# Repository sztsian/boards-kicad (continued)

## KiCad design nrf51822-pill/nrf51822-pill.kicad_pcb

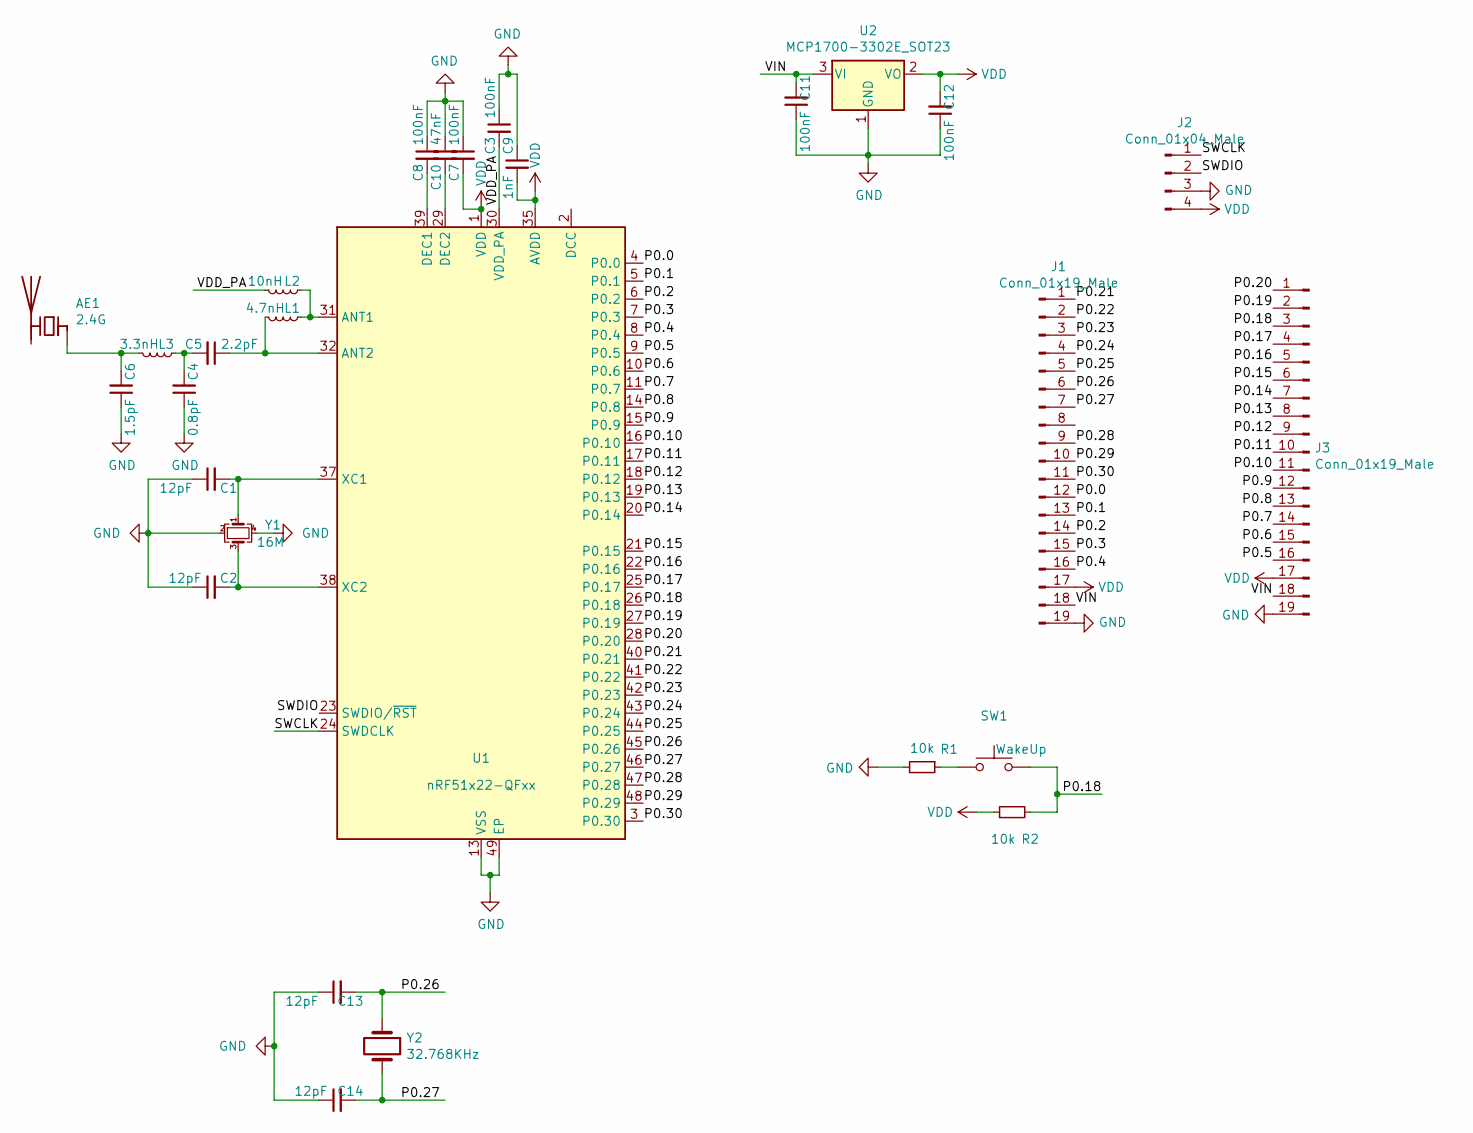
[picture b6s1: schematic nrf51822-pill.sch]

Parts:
AE1: 2.4G; Texas_SWRA117D_2.4GHz_Left
C1, C2, C13, C14: 12pF; C_0603_1608Metric
C3, C7, C8, C11, C12: 100nF; C_0603_1608Metric
C4: 0.8pF; C_0603_1608Metric
C5: 2.2pF; C_0603_1608Metric
C6: 1.5pF; C_0603_1608Metric
C9: 1nF; C_0603_1608Metric
C10: 47nF; C_0603_1608Metric
J1, J3: Conn_01x19_Male; PinHeader_1x19_P2.54mm_Vertical
J2: Conn_01x04_Male; PinHeader_1x04_P2.54mm_Vertical
L1: 4.7nH; L_0603_1608Metric
L2: 10nH; L_0603_1608Metric
L3: 3.3nH; L_0603_1608Metric
R1, R2: 10k; R_0603_1608Metric
SW1: WakeUp; smd_push
U1: nRF51x22-QFxx; QFN-48-1EP_6x6mm_P0.4mm_EP4.6x4.6mm
U2: MCP1700-3302E_SOT23; SOT-23
Y1: 16M; Crystal_SMD_2520-4Pin_2.5x2.0mm
Y2: 32.768KHz; Crystal_SMD_3215-2Pin_3.2x1.5mm

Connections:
/P0.0: J1.12, U1.4 (P0.0)
/P0.1: J1.13, U1.5 (P0.1)
/P0.2: J1.14, U1.6 (P0.2)
/P0.3: J1.15, U1.7 (P0.3)
/P0.4: J1.16, U1.8 (P0.4)
/P0.5: J3.16, U1.9 (P0.5)
/P0.6: J3.15, U1.10 (P0.6)
/P0.7: J3.14, U1.11 (P0.7)
/P0.8: J3.13, U1.14 (P0.8)
/P0.9: J3.12, U1.15 (P0.9)
/P0.10: J3.11, U1.16 (P0.10)
/P0.11: J3.10, U1.17 (P0.11)
/P0.12: J3.9, U1.18 (P0.12)
/P0.13: J3.8, U1.19 (P0.13)
/P0.14: J3.7, U1.20 (P0.14)
/P0.15: J3.6, U1.21 (P0.15)
/P0.16: J3.5, U1.22 (P0.16)
/P0.17: J3.4, U1.25 (P0.17)
/P0.18: J3.3, R2.2, SW1.2, U1.26 (P0.18)
/P0.19: J3.2, U1.27 (P0.19)
/P0.20: J3.1, U1.28 (P0.20)
/P0.21: J1.1, U1.40 (P0.21)
/P0.22: J1.2, U1.41 (P0.22)
/P0.23: J1.3, U1.42 (P0.23)
/P0.24: J1.4, U1.43 (P0.24)
/P0.25: J1.5, U1.44 (P0.25)
/P0.26: C13.2, J1.6, U1.45 (P0.26), Y2.1
/P0.27: C14.2, J1.7, U1.46 (P0.27), Y2.2
/P0.28: J1.9, U1.47 (P0.28)
/P0.29: J1.10, U1.48 (P0.29)
/P0.30: J1.11, U1.3 (P0.30)
/SWCLK: J2.1, U1.24 (SWDCLK)
/SWDIO: J2.2, U1.23 (SWDIO/~RST)
/VDD_PA: C3.2, L2.2, U1.30 (VDD_PA)
/VIN: C11.2, J1.18, J3.18, U2.3 (VI)
GND: C1.1, C2.1, C3.1, C4.1, C6.1, C7.1, C8.1, C9.1, C10.1, C11.1, C12.1, C13.1, C14.1, J1.19, J2.3, J3.19, R1.2, U1.13 (VSS), U1.33 (VSS), U1.34 (VSS), U1.49 (EP), U2.1 (GND), Y1.2, Y1.4
unnamed: AE1.1 (FEED), C6.2, L3.2
unnamed: C1.2, U1.37 (XC1), Y1.1
unnamed: C2.2, U1.38 (XC2), Y1.3
unnamed: C4.2, C5.2, L3.1
unnamed: C5.1, L1.2, U1.32 (ANT2)
unnamed: C8.2, U1.39 (DEC1)
unnamed: C10.2, U1.29 (DEC2)
unnamed: L1.1, L2.1, U1.31 (ANT1)
unnamed: R1.1, SW1.1
VDD: C7.2, C9.2, C12.2, J1.17, J2.4, J3.17, R2.1, U1.1 (VDD), U1.12 (VDD), U1.35 (AVDD), U1.36 (AVDD), U2.2 (VO)

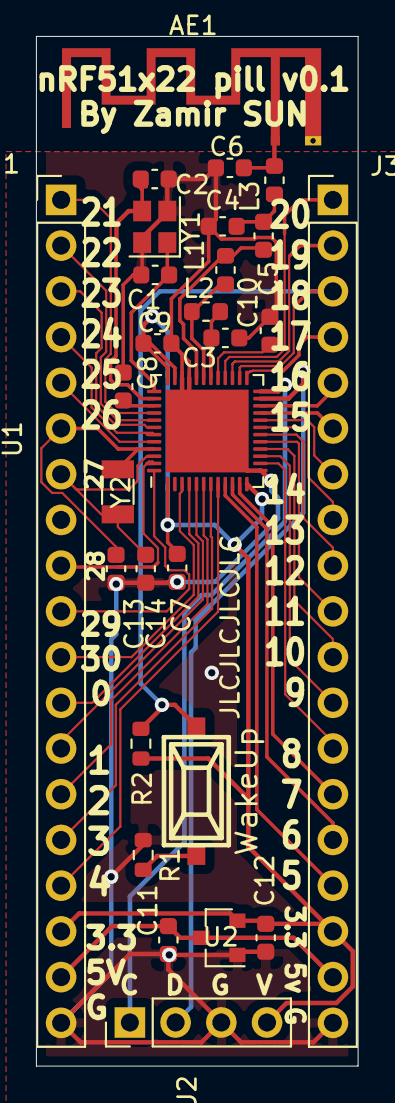
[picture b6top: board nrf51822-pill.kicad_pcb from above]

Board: 2 copper layers, 17.9 x 57.2 mm, 28 parts (0 on the bottom side), 46 nets.

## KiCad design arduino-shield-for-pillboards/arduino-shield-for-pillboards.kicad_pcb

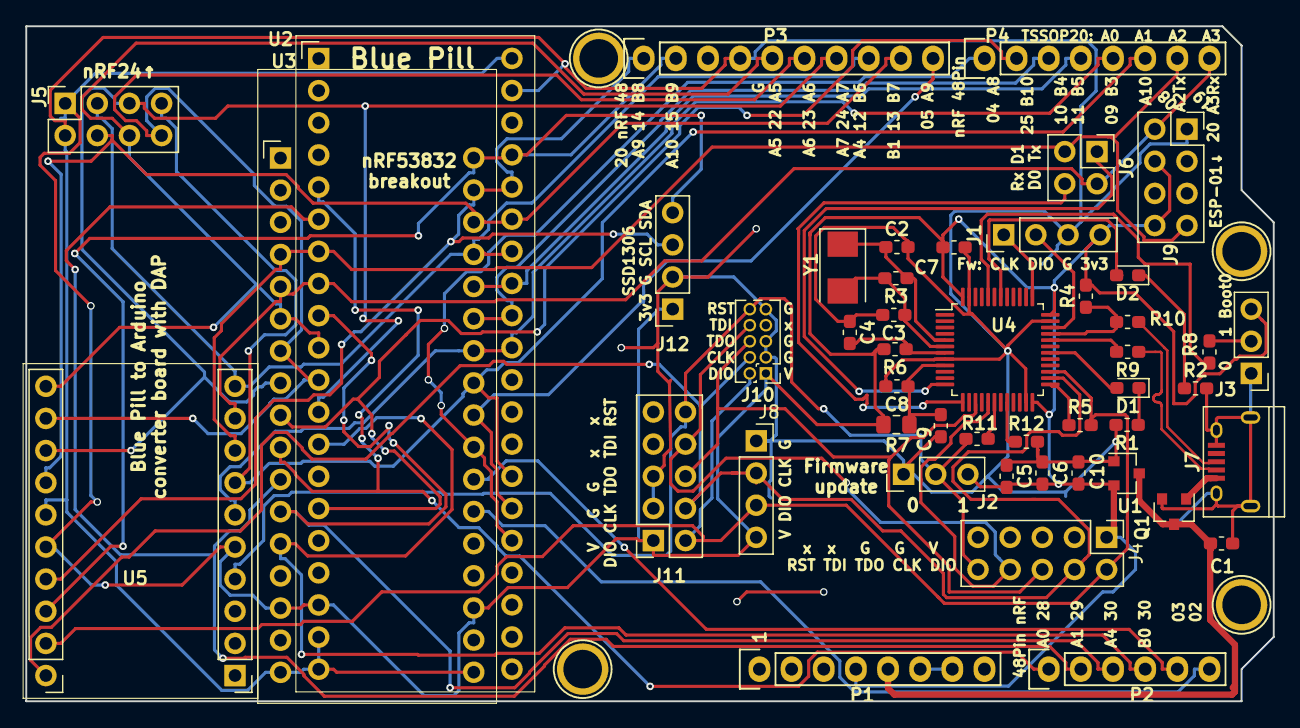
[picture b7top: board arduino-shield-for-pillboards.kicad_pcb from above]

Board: 2 copper layers, 98.6 x 53.3 mm, 51 parts (0 on the bottom side), 52 nets.

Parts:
C1, C4: C_Small; C_0603_1608Metric_Pad1.05x0.95mm_HandSolder
C2, C3: 20p; C_0603_1608Metric_Pad1.05x0.95mm_HandSolder
C5, C6, C7: 0.1u; C_0603_1608Metric_Pad1.05x0.95mm_HandSolder
C8: 10n; C_0603_1608Metric_Pad1.05x0.95mm_HandSolder
C9: 2.2u; C_0603_1608Metric_Pad1.05x0.95mm_HandSolder
C10: 100nF; C_0603_1608Metric_Pad1.05x0.95mm_HandSolder
D1: LED_RUN; LED_0603_1608Metric_Pad1.05x0.95mm_HandSolder
D2: LED_CON; LED_0603_1608Metric_Pad1.05x0.95mm_HandSolder
J1: IF_SWD; PinHeader_1x04_P2.54mm_Vertical
J2: UpdateFW; PinHeader_1x03_P2.54mm_Vertical
J3: Boot0; PinHeader_1x03_P2.54mm_Vertical
J4: Conn_ARM_JTAG_SWD_10; PinHeader_2x05_P2.54mm_Vertical
J5: nRF24; PinSocket_2x04_P2.54mm_Vertical
J6: Conn_01x02_Male; PinHeader_2x02_P2.54mm_Vertical
J7: USB_B_Micro; USB_Micro-B_Connector
J8: Blue_Pill_SWD; PinSocket_1x04_P2.54mm_Vertical
J9: ESP-01; PinSocket_2x04_P2.54mm_Vertical
J10: Conn_ARM_JTAG_SWD_10; PinHeader_2x05_P1.27mm_Vertical
J11: TGT_JTAG2; PinSocket_2x05_P2.54mm_Vertical
J12: SSD1306; PinSocket_1x04_P2.54mm_Vertical
P1: Power; Socket_Strip_Arduino_1x08
P2: Analog; Socket_Strip_Arduino_1x06
P3: Digital; Socket_Strip_Arduino_1x10
P4: Digital; Socket_Strip_Arduino_1x08
P5, P6, P7, P8: CONN_01X01; Arduino_1pin
Q1: Si2305(A5); SOT-23
R1, R2, R6, R8, R11, R12: 10k; R_0603_1608Metric_Pad1.05x0.95mm_HandSolder
R3: 1M; R_0603_1608Metric_Pad1.05x0.95mm_HandSolder
R4: 1.5K; R_0603_1608Metric_Pad1.05x0.95mm_HandSolder
R5: 100; R_0603_1608Metric_Pad1.05x0.95mm_HandSolder
R7: 0R; R_0805_2012Metric_Pad1.15x1.40mm_HandSolder
R9, R10: 22; R_0603_1608Metric_Pad1.05x0.95mm_HandSolder
U1: MCP1700-3302E_SOT23; SOT-23
U2: BluePill
U3: nRF52832-Breakout; nRF52832_Breakout
U4: STM32F103C8Tx; LQFP-48_7x7mm_P0.5mm
U5: STM32F0-TSSOP20-board; TSSOP20-board
Y1: 8M; Crystal_SMD_5032-2Pin_5.0x3.2mm

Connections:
3V3: C5.2, C6.2, C7.2, C10.1, J1.4, J2.3, J3.3, J4.1, J5.1, J8.4, J9.4, J9.8, J10.1, J11.1, J12.1, P1.4, R4.2, R6.2, R7.1, U1.2, U2.18, U2.40, U3.15, U3.20, U4.24, U4.36, U4.48, U5.5, U5.16
5V: C1.1, P1.5, Q1.3, U1.3
A0: P2.1, U2.5, U3.10
A1: P2.2, U2.6, U3.11
A2: P2.3, U2.9, U3.12
A3: P2.4, U2.13, U3.13
A4: P2.5, U3.24
A5: P2.6, U3.23
BOOT0: J3.2, R8.2
D0(Rx): J6.2, J9.2, P4.8, U2.8, U3.5, U5.9
D1(Tx): J6.3, J9.7, P4.7, U2.7, U3.4, U5.8
D2: J5.7, P4.6, U2.27, U3.27, U5.7
D3: P4.5, U2.31, U3.28, U5.6
D4: P4.4, U2.33, U3.30
D5: P4.3, U2.32, U3.29
D6: P4.2, U2.15, U3.9
D7: P4.1, U2.25, U3.25
D8: P3.10, U2.26, U3.26
D9: J5.4, P3.9, U2.35, U3.32, U5.14
D10: J5.3, P3.8, U2.34, U3.31, U5.10
D11: J5.5, P3.7, U2.12, U3.8, U5.13
D12: J5.8, P3.6, U2.11, U3.7, U5.12
D13: J5.6, P3.5, U2.10, U3.6, U5.11
GND: C1.2, C2.2, C3.2, C4.1, C5.1, C6.1, C7.1, C8.2, C9.2, C10.2, J1.3, J2.1, J3.1, J4.3, J4.5, J4.9, J5.2, J7.5, J7.6, J8.1, J9.1, J10.3, J10.5, J10.9, J11.3, J11.5, J12.2, P1.6, P1.7, P3.4, Q1.2, R1.2, R2.2, R12.2, U1.1, U2.19, U2.20, U2.39, U3.17, U3.18, U4.8, U4.23, U4.35, U4.47, U5.15
unnamed: C2.1, R3.1, U4.5, Y1.1
unnamed: C3.1, R3.2, U4.6, Y1.2
unnamed: C4.2, R6.1, U4.7
unnamed: C8.1, C9.1, R7.2, U4.9
unnamed: D1.1, R1.1
unnamed: D2.1, R2.1
unnamed: J7.1, Q1.1
unnamed: R5.1, U4.25
unnamed: R8.1, U4.44
unnamed: R11.1, U4.18
unnamed: R12.1, U4.20
PA2-UART2-TX: J6.1, U4.12
PA3-UART2-RX: J6.4, U4.13
PA9-LED-RUN: D1.2, U4.30
PA11: R9.2, U4.32
PA12: R4.1, R10.2, U4.33
PA13-SWDIO-TMS: J1.2, U4.34
PA14-SWCLK-TCK: J1.1, U4.37
PB0-nRST: J2.2, J4.10, J10.10, J11.10, R11.2, U5.4
PB6-LED-CON: D2.2, U4.42
SCL: J12.3, P3.1, U2.36, U3.33, U5.17
SDA: J12.4, P3.2, U2.37, U3.34, U5.18
TCK-SWCLK: J4.4, J8.2, J10.4, J11.4, U4.26, U5.20
TDI: J4.8, J10.8, J11.8, U4.17
TDO: J4.6, J10.6, J11.6, U4.15
TMS-SWDIO: J4.2, J8.3, J10.2, J11.2, R5.2, U4.27, U5.19
USB-D+: J7.3, R10.1
USB-D-: J7.2, R9.1

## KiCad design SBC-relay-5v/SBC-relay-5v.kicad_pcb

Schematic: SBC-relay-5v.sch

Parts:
C1, C2: 10uF; C_0603_1608Metric_Pad1.05x0.95mm_HandSolder
C3: 100nF; C_0603_1608Metric_Pad1.05x0.95mm_HandSolder
C4, C5: 22pF; C_0603_1608Metric_Pad1.05x0.95mm_HandSolder
D1, D9: 1N4007; D_0603_1608Metric_Pad1.05x0.95mm_HandSolder
D2: LED_IN; LED_0603_1608Metric_Pad1.05x0.95mm_HandSolder
D3: USB1; LED_0603_1608Metric_Pad1.05x0.95mm_HandSolder
D4: USB2; LED_0603_1608Metric_Pad1.05x0.95mm_HandSolder
D5: USB5; LED_0603_1608Metric_Pad1.05x0.95mm_HandSolder
D6: USB6; LED_0603_1608Metric_Pad1.05x0.95mm_HandSolder
D7: USB3; LED_0603_1608Metric_Pad1.05x0.95mm_HandSolder
D8: USB4; LED_0603_1608Metric_Pad1.05x0.95mm_HandSolder
J1: USB_B_Micro; USB_Micro-B_Connector
J2: PWR_IN; KF762_2P
J3, J4: USB_A_Stacked; USB_A_Wuerth_61400826021_Horizontal_Stacked
J5, J6: USB_A; USB_A_Vertical
K1, K2, K3, K4, K5, K6: SANYOU_SRD_Form_A; Relay_SPST_SANYOU_SRD_Series_Form_A
MK1, MK2, MK3, MK4: M2.5; MountingHole_2.7mm_M2.5
Q1, Q2: S8050; SOT-23_Handsoldering
R1, R3, R4, R5, R6, R8: 10k; R_0603_1608Metric_Pad1.05x0.95mm_HandSolder
R2, R9, R10, R11, R12, R13, R14: 100R; R_0603_1608Metric_Pad1.05x0.95mm_HandSolder
R7: 470; R_0603_1608Metric_Pad1.05x0.95mm_HandSolder
SW1: SW_Flash; smd_push
U1: AP1117-33; SOT-223-3_TabPin2
U2: ESP-12F; ESP-12E
U3: ULN2003; SOIC-16_3.9x9.9mm_P1.27mm
U4: CH340G; SOIC-16_3.9x9.9mm_P1.27mm
Y1: 12M; Crystal_AT310_D3.0mm_L10.0mm_Horizontal

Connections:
3V3_MCU: C2.1, C3.1, Q1.3, R4.2, R5.1, R8.1, U1.2 (VO), U2.1, U2.8, U4.4, U4.16
5V_IN: D9.2, J2.1, K1.1, K2.1, K3.1, K4.1, K5.1, K6.1, R2.1
DTR: Q2.1, R1.1, U4.13
GND_IN: C1.2, C2.2, C3.2, C4.2, C5.2, D2.1 (K), J1.5 (GND), J1.6 (Shield), J2.2, J3.4, J3.8, J3.9, J4.4, J4.8, J4.9, J5.4, J5.5, J6.4, J6.5, R6.1, R9.1, R10.1, R11.1, R12.1, R13.1, R14.1, SW1.2, U1.1 (GND), U2.15, U3.8, U4.1
GPIO0: Q2.3, R7.2, R8.2, U2.18
GPIO4: U2.19, U3.1
GPIO5: U2.20, U3.2
GPIO12: U2.6, U3.3
GPIO13: U2.7, U3.4
GPIO14: U2.5, U3.5
GPIO16: U2.4, U3.6
unnamed: C4.1, U4.7, Y1.1
unnamed: C5.1, U4.8, Y1.2
unnamed: D1.2, J1.1 (VBUS)
unnamed: D2.2 (A), R2.2
unnamed: D3.1 (K), R9.2
unnamed: D3.2 (A), J3.1, K1.3
unnamed: D4.1 (K), R10.2
unnamed: D4.2 (A), J3.5, K2.3
unnamed: D5.1 (K), R11.2
unnamed: D5.2 (A), J5.1, K5.3
unnamed: D6.1 (K), R12.2
unnamed: D6.2 (A), J6.1, K6.3
unnamed: D7.1 (K), R13.2
unnamed: D7.2 (A), J4.1, K3.3
unnamed: D8.1 (K), R14.2
unnamed: D8.2 (A), J4.5, K4.3
unnamed: Q1.2, R1.2
unnamed: Q2.2, R3.2
unnamed: R4.1, U2.3
unnamed: R5.2, U2.17
unnamed: R6.2, U2.16
unnamed: R7.1, SW1.1
RTS: Q1.1, R3.1, U4.14
RXD0: U2.21, U4.2
TXD0: U2.22, U4.3
UCOM: K1.5, K2.5, K3.5, K4.5, K5.5, K6.5, U3.9
USB1: K1.2, U3.11
USB2: K2.2, U3.12
USB3: K3.2, U3.13
USB4: K4.2, U3.14
USB5: K5.2, U3.15
USB6: K6.2, U3.16
USB-D+: J1.3 (D+), U4.5
USB-D-: J1.2 (D-), U4.6
VBUS: C1.1, D1.1, D9.1, U1.3 (VI)

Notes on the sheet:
ID_SD and ID_SC PINS: These pins are reserved for HAT ID EEPROM. At boot time this I2C interface will be interrogated to look for an EEPROM that identifes the attached board and allows automagic setup of the GPIOs (and optionally, Linux drivers). DO NOT USE these pins for anything other than attach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
Mounting Holes

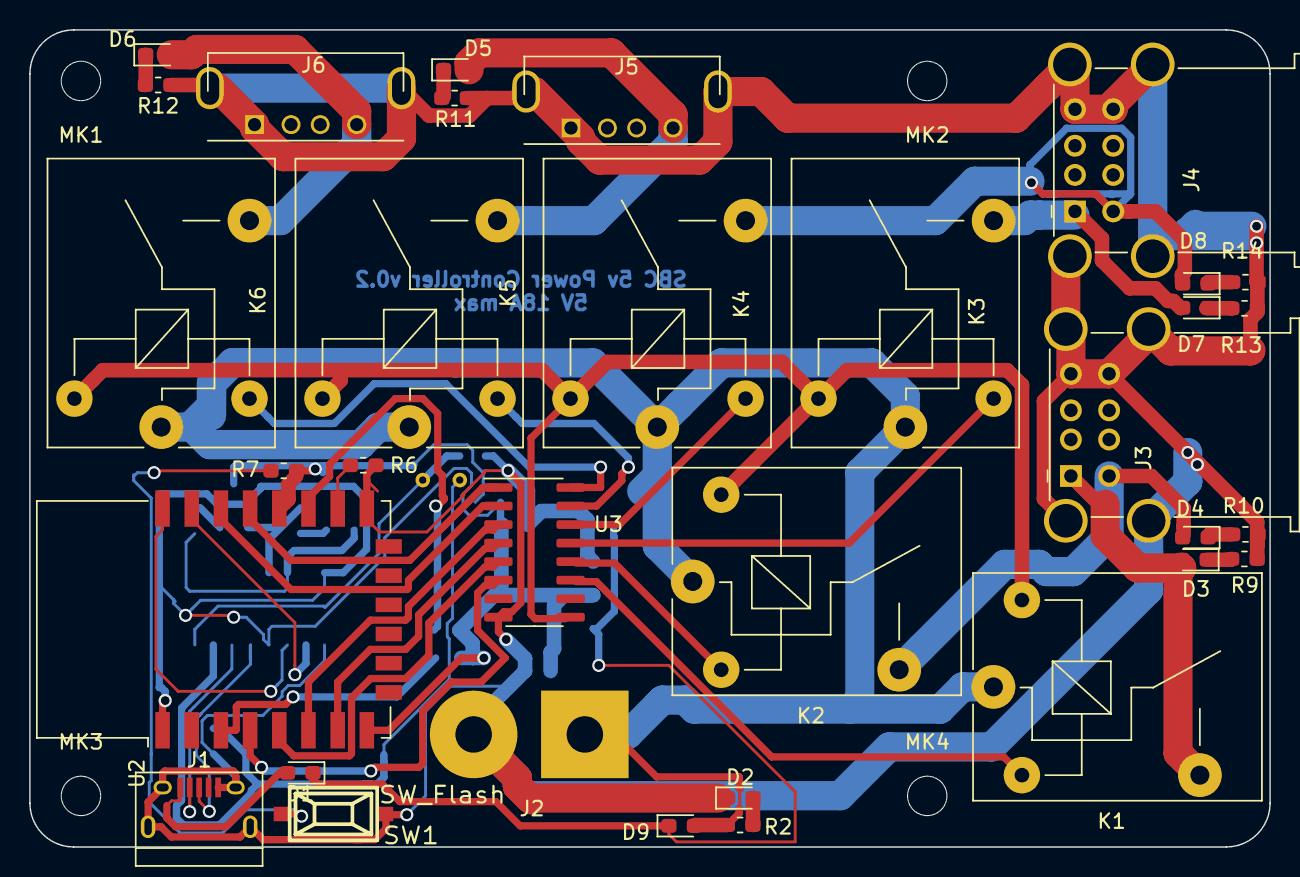
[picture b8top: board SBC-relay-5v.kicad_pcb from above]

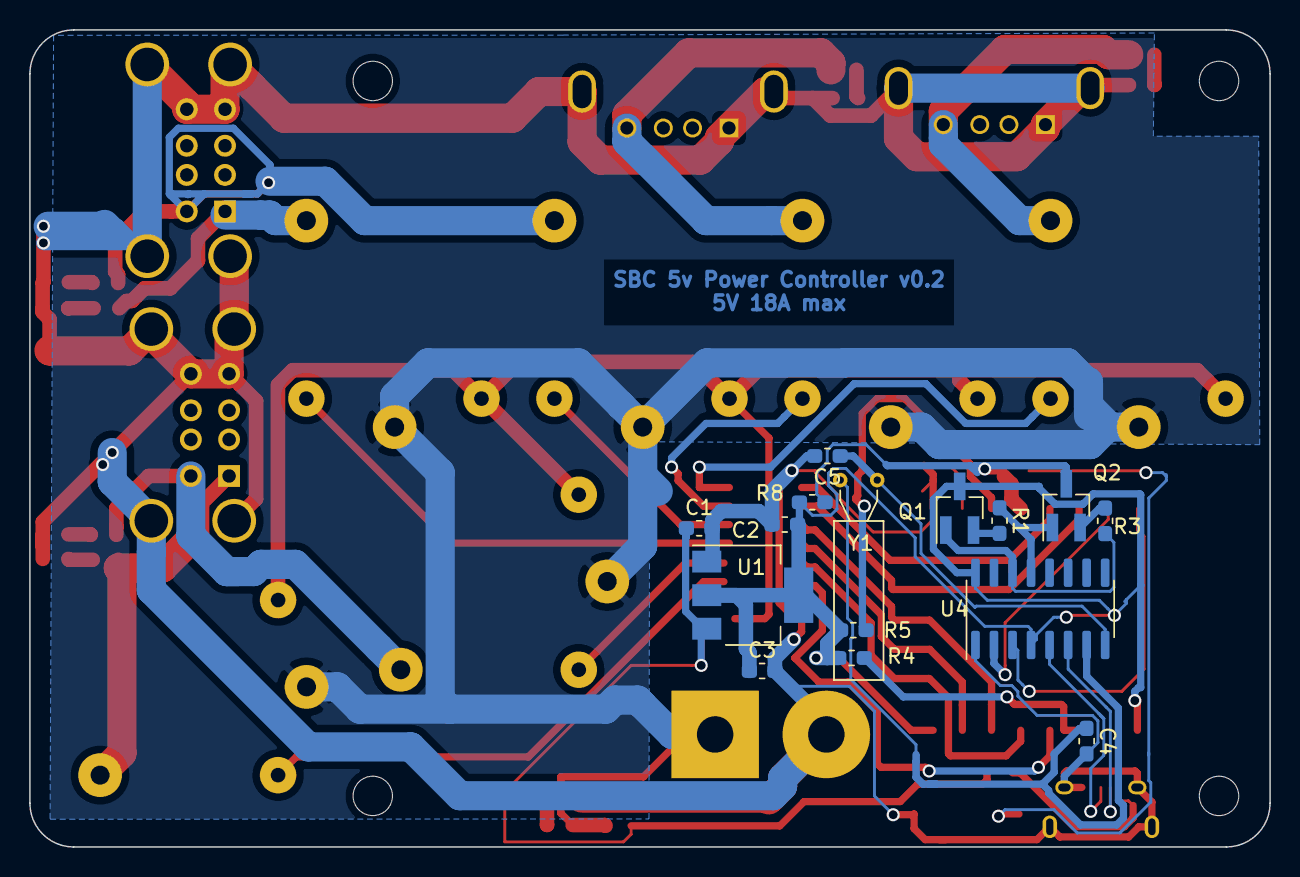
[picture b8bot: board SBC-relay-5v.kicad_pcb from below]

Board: 2 copper layers, 85.0 x 56.0 mm, 52 parts (15 on the bottom side), 46 nets.

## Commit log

2019-03-09 Initial with first version
2019-03-09 Push gitignore
2019-03-16 Fix AMS1117 GND connection
2019-03-16 Fix RX/TX connection to core51822
2019-04-05 Move sensorboard to sub dir
2019-04-05 Update gitignore
2019-04-05 Add STM32F0/GD32F1 TSSPO20 multi-function board
2019-05-02 Add 2.54 2x05 edge mount connector footprint
2019-05-03 Add ST-Link clone style board edge 2x05 2.54 connector
2019-05-03 Add STM32-DIPDAP from https://github.com/ARMmbed/mbed-HDK-Eagle-Projects/tree/master/DAPLink/Probes/STM32-DIPDAP/v1.0.0
2019-05-03 Add another on-board ARM debugger based on STM32F103
2019-05-03 sensorboard: Add DAP firmware
    X893-CMSIS-DAP-V2-F103.hex: Works on STM32F103C8T6 without drag and drop
    support. Source: https://github.com/x893/CMSIS-DAP/blob/7b0a7e3f4278e640fc8ff13df3741442c2a22bae/Firmware/STM32/hex/CMSIS-DAP-V2-F103.hex
    stm32f103xb*: Bootloader and DAPLink firmware for STM32F103CB, support
    drag and drop flash. Build on top of
    https://github.com/ARMmbed/DAPLink/tree/1c83c6543efb93463cbc11ee700d2a07675a7a2f
    with customized projects
2019-05-04 Fix ob-stm32f103 for BOM
2019-05-28 stm32-tssop20board: Fix capacitor for oscillator
2019-05-30 Remove STM32-DIPDAP as it do not work.
2019-09-18 Add board for LQFP48 Blue Pill compatible board of STM32/GD32
2019-09-22 STM32_Blue_Pill: Move all vias out of pads for SMT
2019-09-26 Update for some staged changes. Not sure what has changed actually
2019-09-26 STM32_Blue_Pill: Move all resisters and capacitors to same side for JLC SMT
2019-10-06 WIP: Add initial version of 5V SBC power controller
2020-02-23 Add modified version of SBC-relay-5v
2021-02-14 Add arduino-shield-for-pillboards
2021-11-23 Add nrf51822 pill
2021-11-23 Add nrf24lu1 USB dongle
2021-11-23 Add cc2544 dongle. Note the nrf24lu1p on this does not work.
2021-11-23 Add EFR32 baseboard
2021-12-11 wch-debugger: Add WCH-Link and CH552G JTAG.
    Tested on pcb.
2021-12-11 Add Tuya WB3L / ZS3L base board.
    Tested on PCB.
2021-12-11 Add ESP32 wallswitch control board (for Zhixianglian wifi switch)
    Tested on top of 智相连 Tuya WiFi smart switch 1 gang and 3 gang.
